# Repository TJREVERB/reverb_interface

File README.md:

# TJREVERB Interface Boards
Interface board rework, moved from Eagle to Kicad

The board provides power connections from the EPS and data connections from the flight computer to various components.

APRS and Iridium (through a MAX3232) are connected to UART, and can be selected between hardware UART and software/converter UART using jumpers. software/converter UART uses a converter as the primary UART device, with an option for software bit banging using RPi GPIO as a backup.

There are three branches: USB to UART, SPI to UART (DEPRECATED IN v1.4), and Multicore

The first is similar to the original design, and uses a USB to UART converter. 

The second uses an SPI to UART converter so that we can send data through the main Pi header instead of pogo pins or USB pads. DEPRECATED DUE TO DIFFICULTY IN SOFTWARE IMPLEMENTATION

The third uses an external AVR microcontroller as a secondary core, to be used for IO operations, specifically as an SPI/I2C to UART converter and an I2C buffer for sending delayed commands to the EPS (e.g. sending bus reset after a delay to give the pi enough time to exit script)

All branches include connections to bitbang uart instead of using the converter.

## Versions
v1.0 initial

v1.1 routing improvements

v1.2 fabricated first, received 10/24/21

v1.3 adds major corrections for circuitry

v1.4 introduces the new multicore branch

v1.5 replaces LSM9DS1 IMU with BNO055

v1.6 adds RTC and battery

v2.0 CAD compatibility check, fabbed as v2 on 11/28/21

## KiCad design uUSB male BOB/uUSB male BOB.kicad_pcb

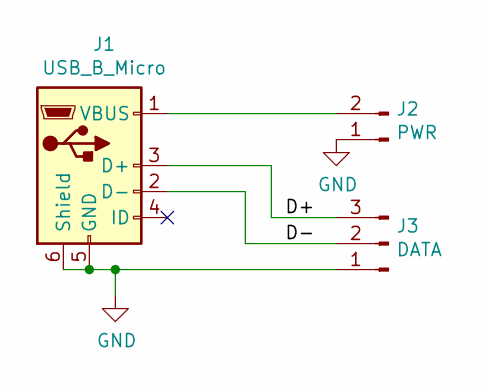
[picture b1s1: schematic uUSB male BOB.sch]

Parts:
J1: USB_B_Micro; USB3150-30-130-A
J2: PWR; PinHeader_1x02_P2.54mm_Vertical
J3: DATA; PinHeader_1x03_P2.54mm_Vertical

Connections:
/D+: J1.3 (D+), J3.3
/D-: J1.2 (D-), J3.2
GND: J1.5 (GND), J1.6 (Shield), J2.1, J3.1
unnamed: J1.1 (VBUS), J2.2

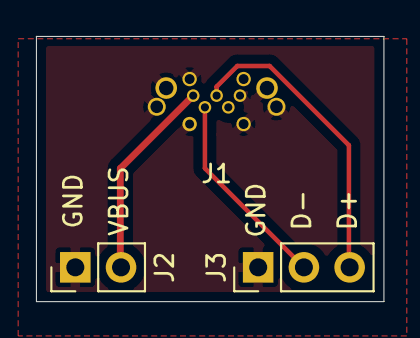
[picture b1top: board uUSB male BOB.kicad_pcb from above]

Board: 2 copper layers, 19.3 x 14.7 mm, 3 parts (0 on the bottom side), 4 nets.

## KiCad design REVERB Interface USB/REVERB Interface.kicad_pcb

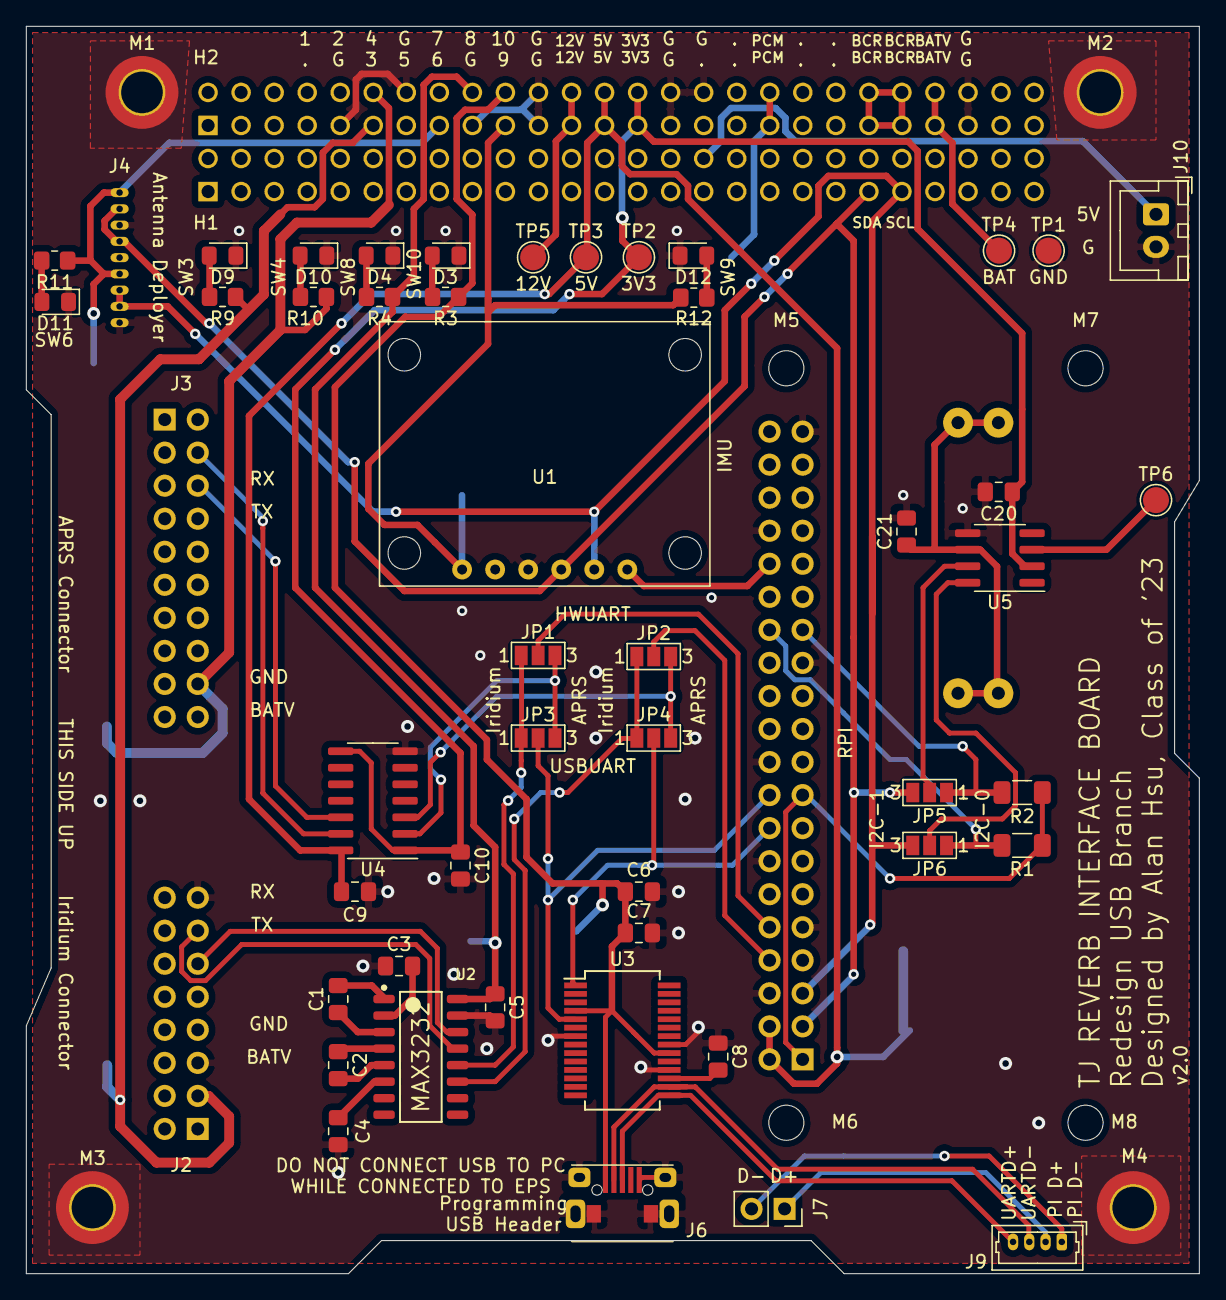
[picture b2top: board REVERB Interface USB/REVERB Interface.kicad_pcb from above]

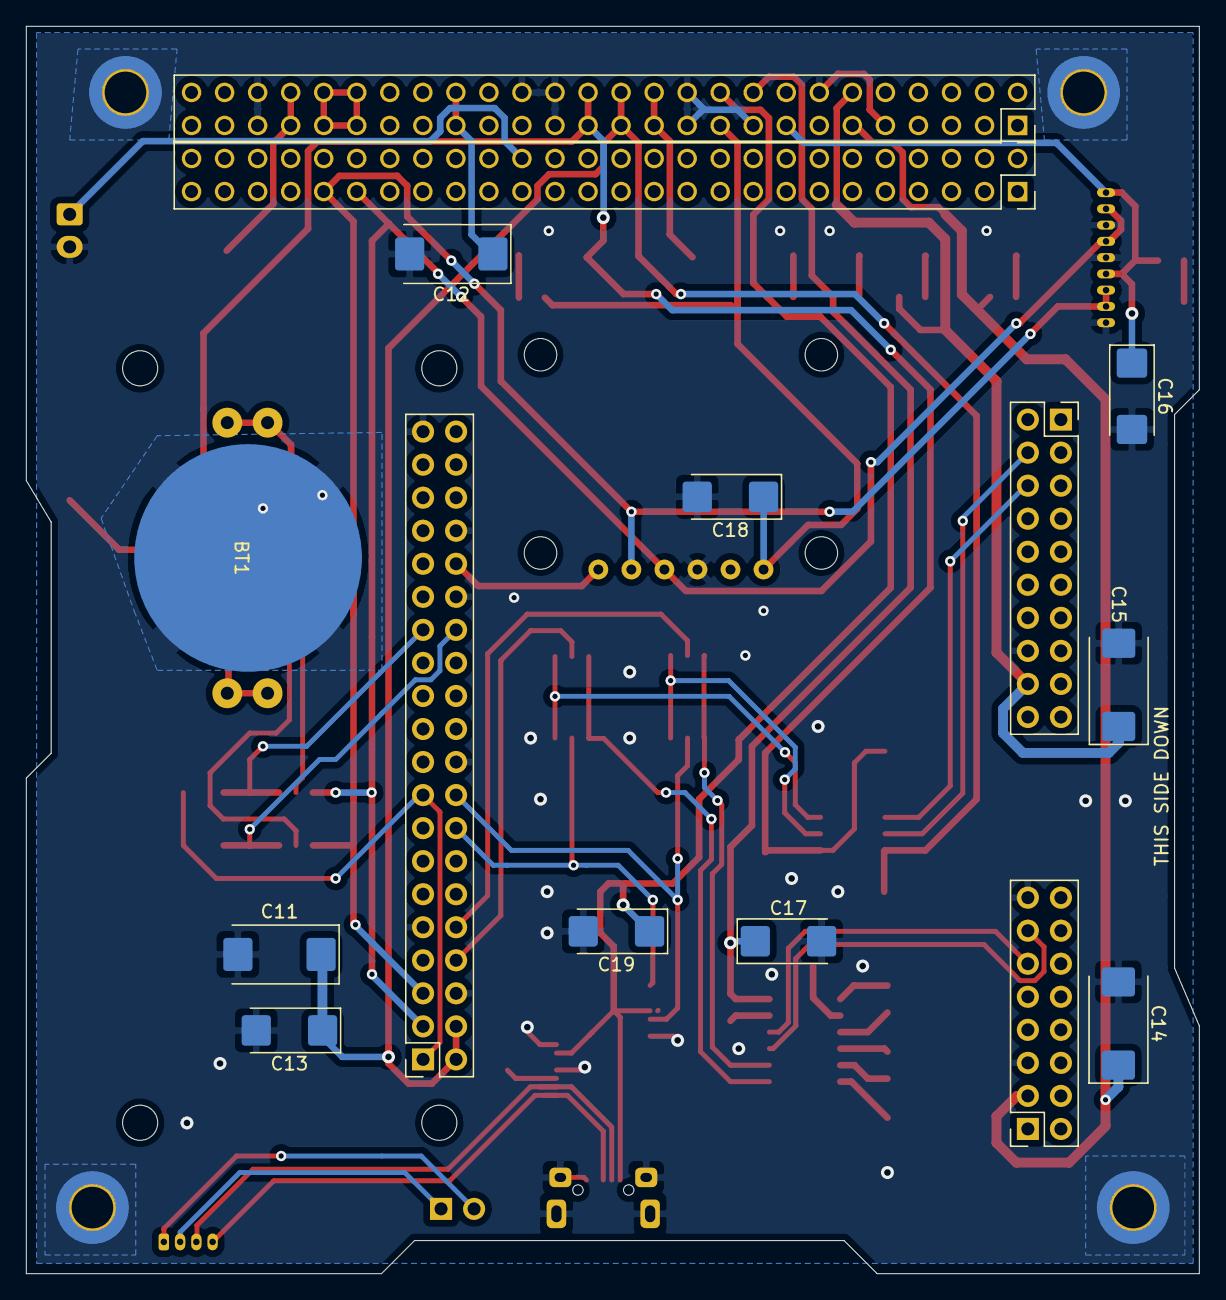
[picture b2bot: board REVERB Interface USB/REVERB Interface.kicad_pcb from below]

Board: 2 copper layers, 90.2 x 95.9 mm, 71 parts (15 on the bottom side), 53 nets.

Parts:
BT1: CR-2032; CR2032-LINX-HLD-001-THM
C1, C5, C7, C9, C10: 0.1uF; C_0805_2012Metric_Pad1.18x1.45mm_HandSolder
C2, C3, C4: 0.47uF; C_0805_2012Metric_Pad1.18x1.45mm_HandSolder
C6: 4.7uF; C_0805_2012Metric_Pad1.18x1.45mm_HandSolder
C8, C20, C21: 1uF; C_0805_2012Metric_Pad1.18x1.45mm_HandSolder
C11, C12, C14, C15: 100uF; CP_EIA-7343-43_Kemet-X_Pad2.25x2.55mm_HandSolder
C13, C16, C17, C18, C19: 22uF; CP_EIA-6032-28_Kemet-C_Pad2.25x2.35mm_HandSolder
D3, D4, D9, D10, D11, D12: RED; LED_0805_2012Metric_Pad1.15x1.40mm_HandSolder
H1: EPS Stack Header 2; PinSocket_2x26_P2.54mm_Vertical
H2: EPS Stack Header 1; PinSocket_2x26_P2.54mm_Vertical
J1: RPiZeroW; PinSocket_2x20_P2.54mm_Vertical
J2: Iridium; PinSocket_2x08_P2.54mm_Vertical
J3: APRS; PinSocket_2x10_P2.54mm_Vertical
J4: Antenna; 1.25mmPitchHeader
J6: USB_B_Micro; AdafruitMicroB
J7: USB; PinSocket_1x02_P2.54mm_Vertical
J9: USB SWITCH; Molex_PicoBlade_53047-0410_1x04_P1.25mm_Vertical
J10: USBPWR; JST_XH_B2B-XH-A_1x02_P2.50mm_Vertical
JP1: HWRX; SolderJumper-3_P1.3mm_Open_Pad1.0x1.5mm_NumberLabels
JP2: HWTX; SolderJumper-3_P1.3mm_Open_Pad1.0x1.5mm_NumberLabels
JP3: USBUARTRX; SolderJumper-3_P1.3mm_Open_Pad1.0x1.5mm_NumberLabels
JP4: USBUARTTX; SolderJumper-3_P1.3mm_Open_Pad1.0x1.5mm_NumberLabels
JP5: RTCSDA; SolderJumper-3_P1.3mm_Open_Pad1.0x1.5mm_NumberLabels
JP6: RTCSCL; SolderJumper-3_P1.3mm_Open_Pad1.0x1.5mm_NumberLabels
M1, M2, M3, M4: Stack Mounting Hole; MountingHole_3.2mm_M3_DIN965_Pad_TopBottom
M5, M6, M7, M8: PiMount; MountingHole_2.7mm_M2.5
R1, R2: 2.2K; R_1206_3216Metric_Pad1.30x1.75mm_HandSolder
R3, R4, R11, R12: 1K; R_0805_2012Metric_Pad1.20x1.40mm_HandSolder
R9, R10: 5K; R_0805_2012Metric_Pad1.20x1.40mm_HandSolder
TP1: GND; TestPoint_Pad_D2.0mm
TP2: 3V3; TestPoint_Pad_D2.0mm
TP3: 5V; TestPoint_Pad_D2.0mm
TP4: BAT; TestPoint_Pad_D2.0mm
TP5: 12V; TestPoint_Pad_D2.0mm
TP6: SQWV; TestPoint_Pad_D2.0mm
U1: IMU; BNO055
U2: MAX3232; Texas_Instruments-MAX3232ID-Level_A
U3: CY7C65213-28PVXI; SSOP-28_5.3x10.2mm_P0.65mm
U4: TXB0104D; SOIC-14_3.9x8.7mm_P1.27mm
U5: DS3232M; SOIC-8_3.9x4.9mm_P1.27mm

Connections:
+3.3VA: J1.1, J1.17, R1.1, R2.1
+3V3: C10.1, C20.1, H2.27, H2.28, TP2.1, U4.1, U4.8, U5.2
+5V: C9.1, C11.1, C13.1, H2.25, H2.26, J1.2, J1.4, TP3.1, U4.14
+12V: H2.23, H2.24, TP5.1
+BATT: BT1.1, C21.1, U5.6
/5VUSBCHG: H1.32, J10.1
/APRSRX: JP1.3, JP3.3, U4.2
/APRSRX_Shift: J3.4, U4.13
/APRSTX: JP2.3, JP4.3, U4.3
/APRSTX_Shift: J3.6, U4.12
/BCR_OUT: H2.41, H2.42, H2.43, H2.44
/D+: J6.3, J9.4, U3.15
/D-: J6.2, J9.3, U3.16
/EPSSCL: H1.43, J1.5, J4.7, J4.8, JP6.3, U1.5
/EPSSDA: H1.41, J1.3, J4.2, J4.4, JP5.3, U1.4
/HWRX: J1.10, JP1.2
/HWTX: J1.8, JP2.2
/IMURST: J1.32, U1.6
/PCM_IN: C12.1, H2.35, H2.36
/PID+: J7.1, J9.2
/PID-: J7.2, J9.1
/R1IN: J2.13, U2.13
/R1OUT: JP1.1, JP3.1, U2.12
/RTCSCL: JP6.2, U5.8
/RTCSDA: JP5.2, U5.7
/SCL0: J1.28, JP6.1, R1.2
/SDA0: J1.27, JP5.1, R2.2
/SQW: TP6.1, U5.3
/SW3: C14.1, H2.11, J2.3, R9.1
/SW4: C15.1, H2.12, J3.18, R10.1
/SW6: C16.1, H2.15, J4.1, J4.6, R11.1
/SW8: C5.1, C17.1, H2.18, R4.1, U2.16
/SW9: C18.1, H2.19, R12.1, U1.1
/SW10: C6.1, C7.1, C19.1, H2.20, J6.1, R3.1, U3.4, U3.20
/T1IN: JP2.1, JP4.1, U2.11
/T1OUT: J2.11, U2.14
/USBUARTRX: J1.18, JP3.2, U3.5
/USBUARTTX: J1.16, JP4.2, U3.1
GND: BT1.2, C3.1, C4.1, C5.2, C6.2, C7.2, C8.2, C9.2, C10.2, C11.2, C12.2, C13.2, C14.2, C15.2, C16.2, C17.2, C18.2, C19.2, C20.2, C21.2, D3.1, D4.1, D9.1, D10.1, D11.1, D12.1, H2.9, H2.14, H2.17, H2.21, H2.22, H2.29, H2.30, H2.32, H2.47, H2.48, J1.6, J1.9, J1.14, J1.20, J1.25, J1.30, J1.34, J1.39, J2.5, J2.15, J3.16, J4.3, J4.5, J4.9, J6.5, J6.6, J10.2, M1.1, M2.1, M3.1, M4.1, TP1.1, U1.3, U2.15, U3.7, U3.18, U3.21, U4.7, U5.5
unnamed: C1.1, U2.3
unnamed: C1.2, U2.1
unnamed: C2.1, U2.4
unnamed: C2.2, U2.5
unnamed: C3.2, U2.2
unnamed: C4.2, U2.6
unnamed: C8.1, U3.17
unnamed: D3.2, R3.2
unnamed: D4.2, R4.2
unnamed: D9.2, R9.2
unnamed: D10.2, R10.2
unnamed: D11.2, R11.2
unnamed: D12.2, R12.2
VBUS: H2.45, H2.46, TP4.1

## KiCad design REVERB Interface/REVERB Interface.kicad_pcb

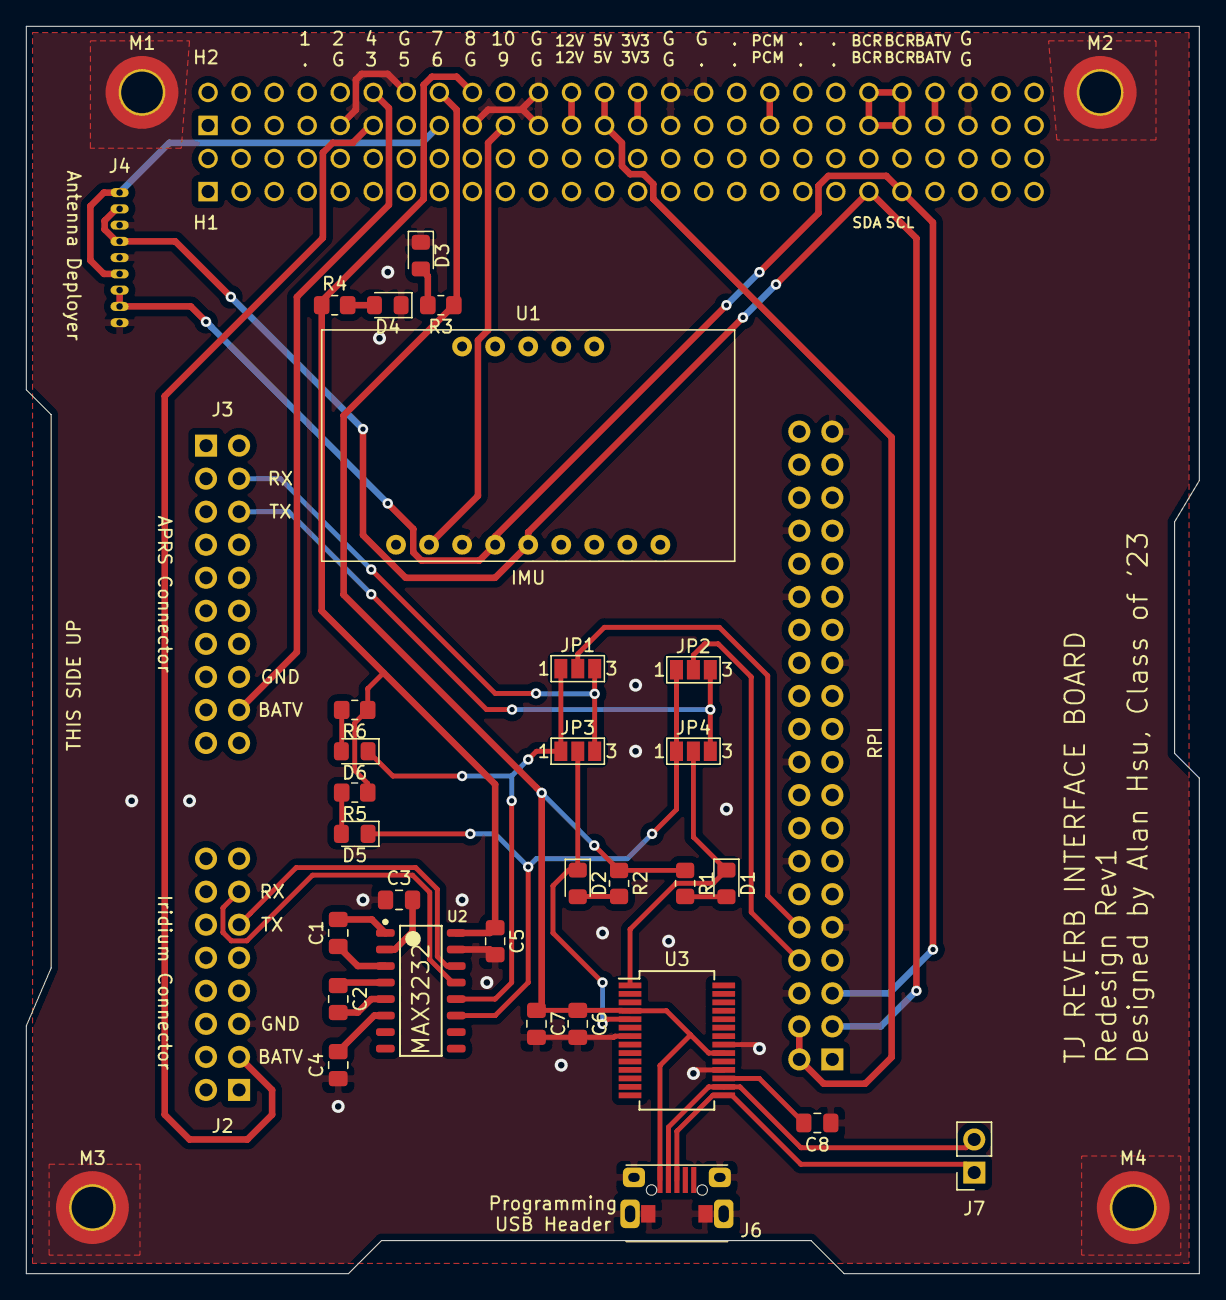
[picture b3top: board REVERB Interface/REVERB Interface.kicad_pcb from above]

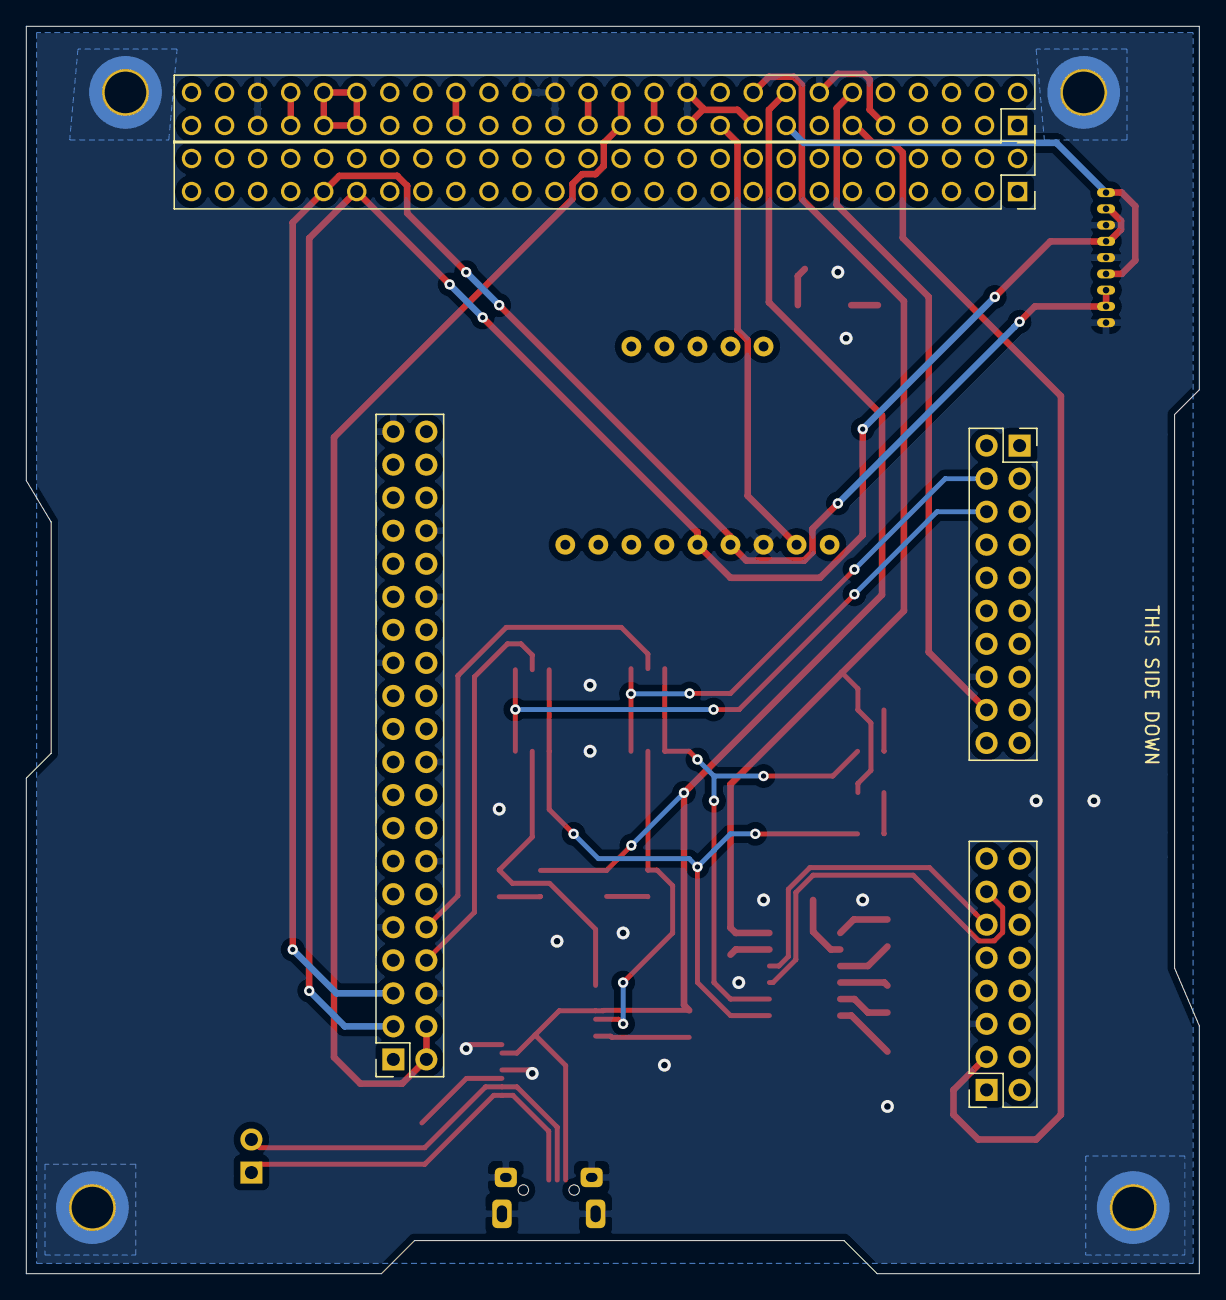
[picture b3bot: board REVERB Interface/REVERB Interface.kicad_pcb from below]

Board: 2 copper layers, 90.2 x 95.9 mm, 39 parts (5 on the bottom side), 40 nets.

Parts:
C1, C5, C7: 0.1uF; C_0805_2012Metric_Pad1.18x1.45mm_HandSolder
C2, C3, C4: 0.47uF; C_0805_2012Metric_Pad1.18x1.45mm_HandSolder
C6: 4.7uF; C_0805_2012Metric_Pad1.18x1.45mm_HandSolder
C8: 1uF; C_0805_2012Metric_Pad1.18x1.45mm_HandSolder
D1, D3, D4, D5: RED; LED_0805_2012Metric_Pad1.15x1.40mm_HandSolder
D2, D6: GREEN; LED_0805_2012Metric_Pad1.15x1.40mm_HandSolder
H1: EPS Stack Header 2; PinSocket_2x26_P2.54mm_Vertical
H2: EPS Stack Header 1; PinSocket_2x26_P2.54mm_Vertical
J1: RPiZeroW; PinSocket_2x20_P2.54mm_Vertical
J2: Iridium; PinSocket_2x08_P2.54mm_Vertical
J3: APRS; PinSocket_2x10_P2.54mm_Vertical
J4: Antenna; 1.25mmPitchHeader
J6: USB_B_Micro; AdafruitMicroB
J7: USB; PinSocket_1x02_P2.54mm_Vertical
JP1: HWRX; SolderJumper-3_P1.3mm_Open_Pad1.0x1.5mm_NumberLabels
JP2: HWTX; SolderJumper-3_P1.3mm_Open_Pad1.0x1.5mm_NumberLabels
JP3: USBUARTRX; SolderJumper-3_P1.3mm_Open_Pad1.0x1.5mm_NumberLabels
JP4: USBUARTTX; SolderJumper-3_P1.3mm_Open_Pad1.0x1.5mm_NumberLabels
M1, M2, M3, M4: MountingHole_Pad; MountingHole_3.2mm_M3_DIN965_Pad_TopBottom
R1, R2, R3, R4, R5, R6: 1K; R_0805_2012Metric_Pad1.20x1.40mm_HandSolder
U1: LSM9DS1BOB
U2: MAX3232; Texas_Instruments-MAX3232ID
U3: CY7C65213-28PVXI; SSOP-28_5.3x10.2mm_P0.65mm

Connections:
+3V3: H2.27, H2.28
+5V: H2.25, H2.26, J1.2, J1.4
+12V: H2.23, H2.24
/APRSRX: J3.4, JP1.3, JP3.3
/APRSTX: J3.6, JP2.3, JP4.3
/BCR_OUT: H2.41, H2.42, H2.43, H2.44
/D+: J6.3, J7.1, U3.15
/D-: J6.2, J7.2, U3.16
/EPSSCL: H1.43, J1.5, J4.7, J4.8, U1.11
/EPSSDA: H1.41, J1.3, J4.2, J4.4, U1.10
/HWRX: J1.10, JP1.2
/HWTX: J1.8, JP2.2
/PCM_IN: H2.35, H2.36
/R1IN: J2.13, U2.13
/R1OUT: D6.1, JP1.1, JP3.1, U2.12
/SW3: H2.11, J2.3
/SW4: H2.12, J3.18
/SW6: H2.15, J4.1, J4.6
/SW7: C6.1, C7.1, H2.16, J6.1, R1.1, R2.1, R3.1, U3.4, U3.20
/SW8: C5.1, H2.18, R4.1, R5.1, R6.1, U2.16
/SW9: H2.19, U1.13
/T1IN: D5.1, JP2.1, JP4.1, U2.11
/T1OUT: J2.11, U2.14
/USBUARTRX: D2.1, JP3.2, U3.5
/USBUARTTX: D1.1, JP4.2, U3.1
GND: C3.1, C4.1, C5.2, C6.2, C7.2, C8.2, D3.1, D4.1, H2.9, H2.14, H2.17, H2.21, H2.22, H2.29, H2.30, H2.32, H2.47, H2.48, J1.6, J1.9, J1.14, J1.20, J1.25, J1.30, J1.34, J1.39, J2.5, J3.16, J4.3, J4.5, J4.9, J6.5, J6.6, M1.1, M2.1, M3.1, M4.1, U1.12, U2.15, U3.7, U3.18, U3.21
unnamed: C1.1, U2.3
unnamed: C1.2, U2.1
unnamed: C2.1, U2.4
unnamed: C2.2, U2.5
unnamed: C3.2, U2.2
unnamed: C4.2, U2.6
unnamed: C8.1, U3.17
unnamed: D1.2, R1.2
unnamed: D2.2, R2.2
unnamed: D3.2, R3.2
unnamed: D4.2, R4.2
unnamed: D5.2, R5.2
unnamed: D6.2, R6.2
VBUS: H2.45, H2.46

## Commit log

2021-10-03 Establish file structure, add archived versions
2021-10-03 Schematic work: added EPS and Pi Headers
2021-10-03 mounting holes and ground connections
2021-10-05 work
2021-10-06 add capacitors to max3232
2021-10-06 wiring work
2021-10-07 footprint associations
2021-10-07 create board, finish footprint association
2021-10-07 copy old board layout positions
2021-10-07 silkscreen labels
2021-10-07 do stuff
2021-10-09 bunch of work
2021-10-09 add solder jumpers
2021-10-09 routing work
2021-10-10 finsihing up routing
2021-10-10 finishing up for real now
2021-10-10 create spi to uart branch
2021-10-10 fix a via
2021-10-10 Add LDO to convert 5V USB logic to 3V3 UART
2021-10-10 fix silkscreen, add another ground via
2021-10-10 spi edits
2021-10-10 SPI Branch routing
2021-10-10 update silkscreen
2021-10-10 Add RTS and CTS connections to layout
2021-10-11 Add LEDs for all used PDMs
2021-10-13 visual cleanup
2021-10-13 Remove LDO
2021-10-13 Add note regarding usb programming
2021-10-14 Routing EMI considerations
2021-10-15 EMI and SI minmaxing, round 2
2021-10-15 Combined files for smt stencil
    *NOT PANELIZED*
2021-10-15 Replace max3232 footprint, update stencil
2021-10-15 update silkscreen again
2021-10-24 Remove incorrect uart flow control connections, pull CTS low. Improve silkscreen placement
    Issue #3 and Issue #5
2021-10-24 Improve usb branch silkscreen, push v1.3
    #5 Will need to verify required clearance for connector housing later.
2021-10-24 Add bitbang uart connections
    gpio 23 and 24, #2
2021-10-24 Correct RPi symbol GPIO numbers
2021-10-27 Add level shifters, updated sch revision numbers consistent with pcb
2021-10-28 add level shifter to routing
    #1
2021-11-03 Fix USB header placement
2021-11-03 add switch led silkscreen labels
2021-11-04 Deprecate SPI branch, push v1.4, add new "multicore" branch, remove combined board files
2021-11-04 Update documentation
2021-11-05 tie OE high
2021-11-06 Add decoupling
2021-11-08 fix imu implementation, add bno055 compatibility
2021-11-08 fix imu implementation on multicore branch
2021-11-08 add attiny firmware first version
2021-11-09 I have no idea what Im doing with this firmware
2021-11-11 add protocol info
2021-11-11 intermediate commit
2021-11-12 finish bno055 mod, push v1.5
2021-11-12 gerber export
2021-11-15 RI line
2021-11-15 route, edit i2c description
2021-11-16 implement rtc on a pdm
2021-11-16 embed the rtc
2021-11-17 fix some compile time errors
2021-11-17 add footprints, may need to use smaller battery
2021-11-18 3d model updates
2021-11-18 Remove RI line
2021-11-19 add usb switch
2021-11-19 finish routing rtc
2021-11-21 add microusb breakout board
2021-11-22 Move some parts around, remove UART LEDs, .step export, push v1.6
2021-11-26 start on adding i2c-0 option
2021-11-26 add i2c0 option
2021-11-26 tidy up the schematic, for usb branch
2021-11-26 finish tidying up schematics
2021-11-26 new gerber exports
2021-11-28 stack conflict checking
2021-11-28 push v2.0
2021-11-28 remove usb pogo
2021-11-28 remove zips
2021-11-30 move gerbers, add combined branches gerber again
2021-12-04 replace SPI slave with I2C slave
